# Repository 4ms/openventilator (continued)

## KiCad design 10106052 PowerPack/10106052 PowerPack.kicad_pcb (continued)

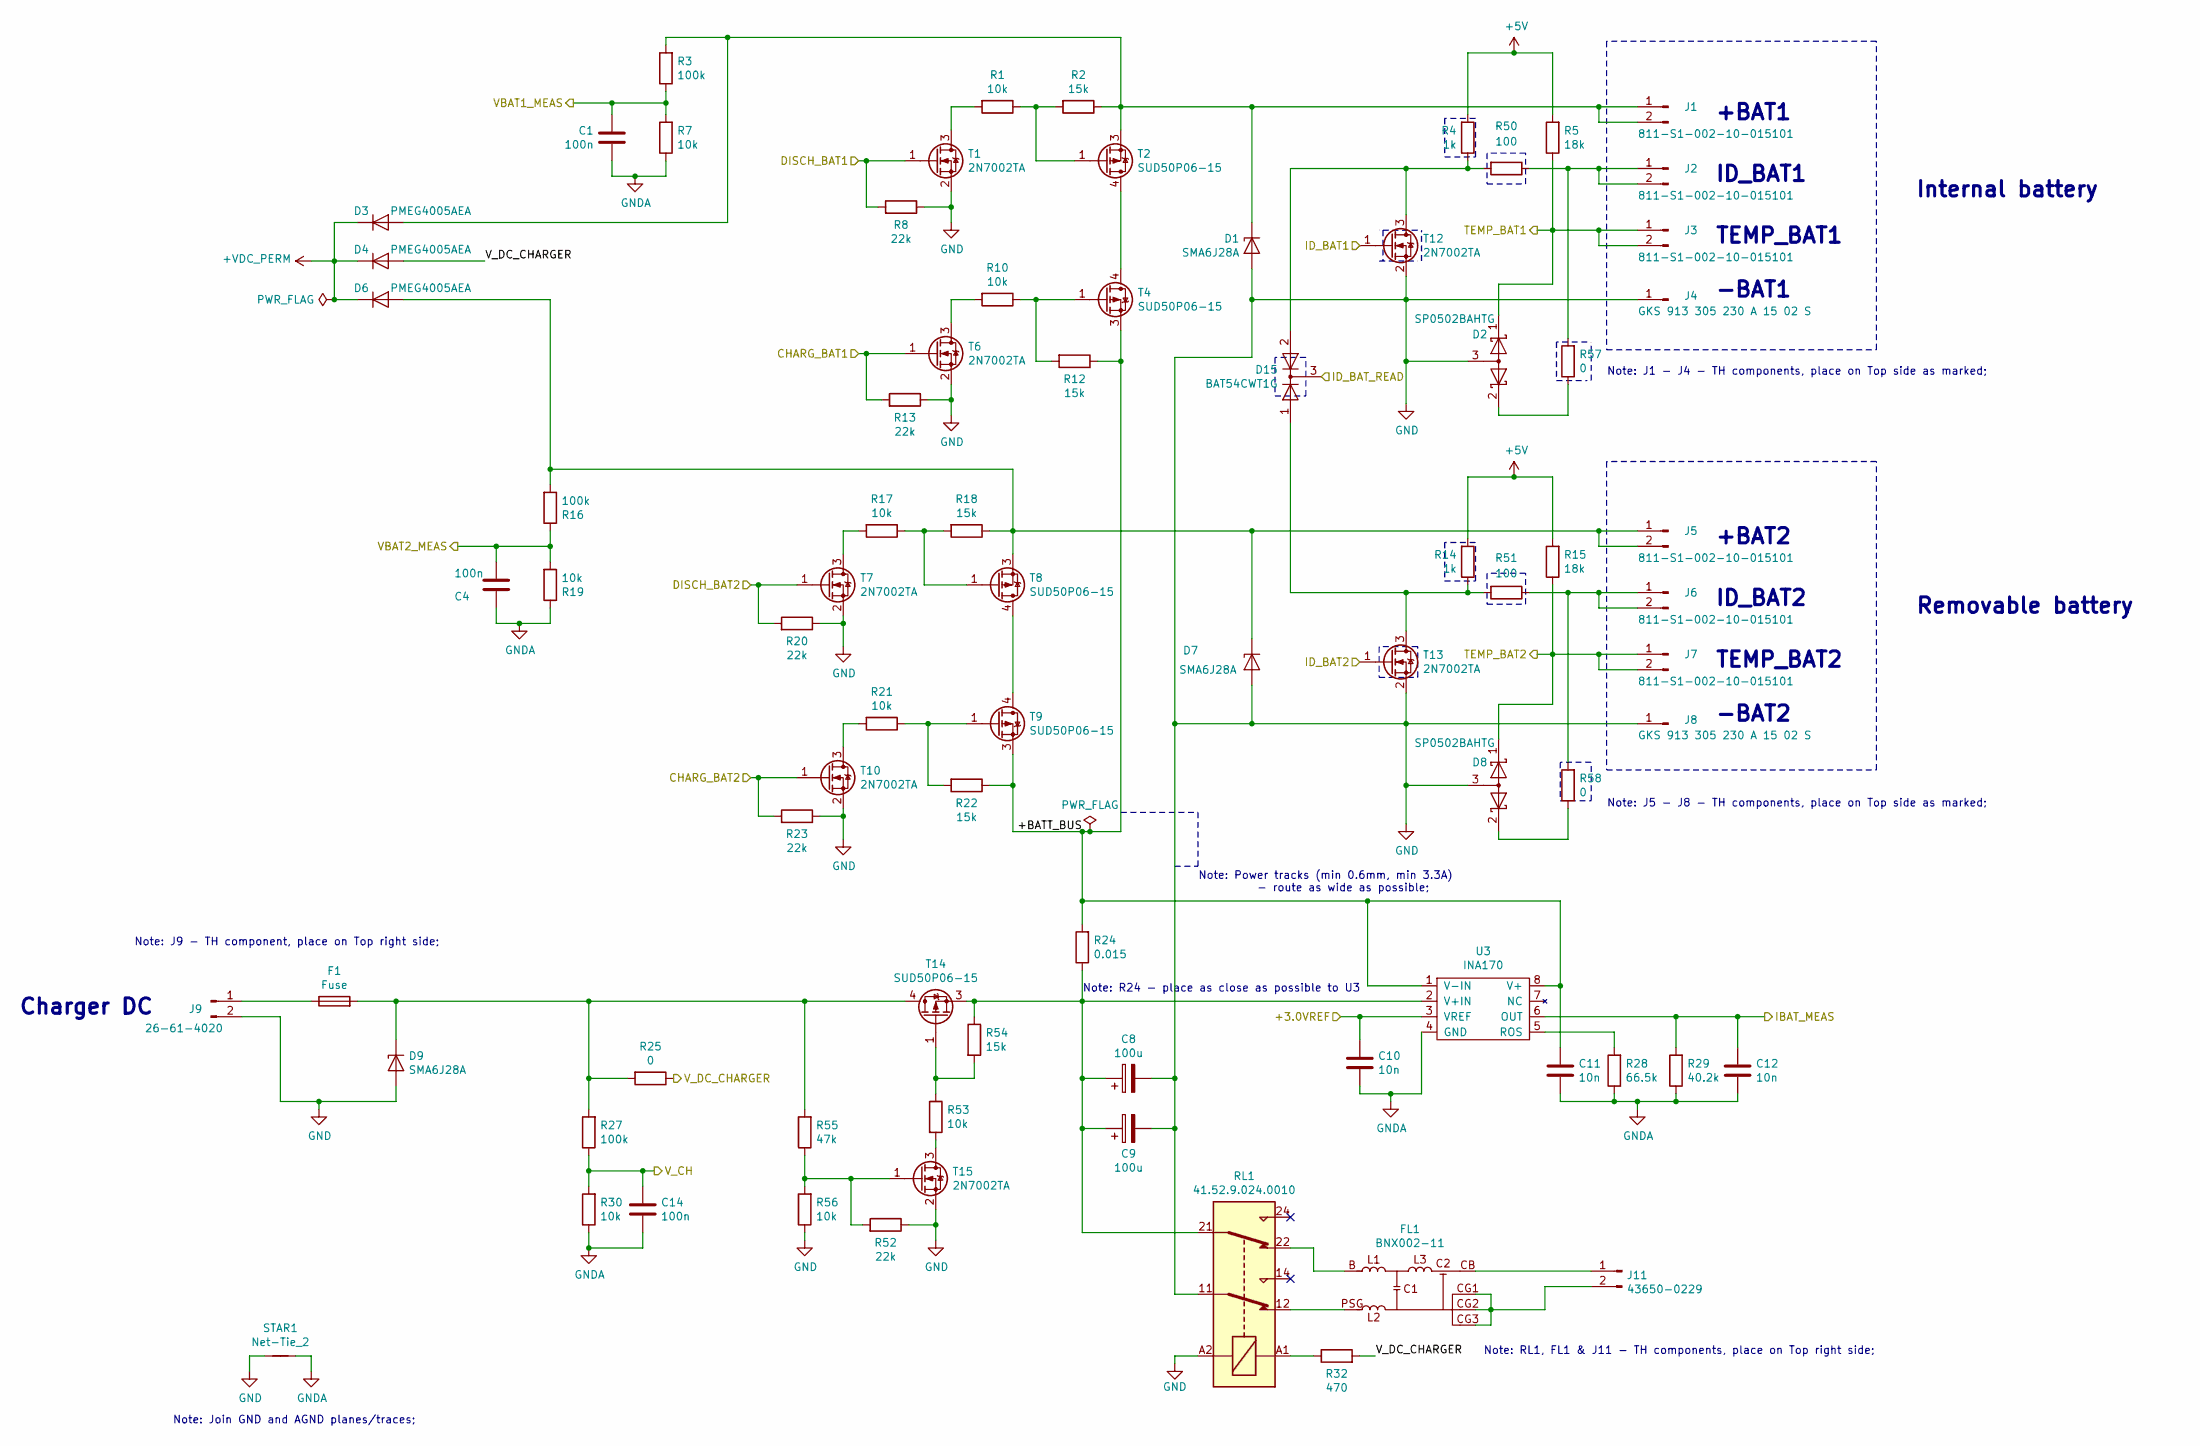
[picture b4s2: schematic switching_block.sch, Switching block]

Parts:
C1, C4, C14: 100n; CAPC1608X86N
C8, C9: 100u; CAPPRD350W60D800H1250
C10, C11, C12: 10n; CAPC1608X86N
D1, D7, D9: SMA6J28A; DIOM5126X203N_SWP
D2, D8: SP0502BAHTG; SOT65P220X110-3N
D3, D4, D6: PMEG4005AEA; SOD2512X110N_SWP
D15: BAT54CWT1G; SOT65P220X110-3N
F1: Fuse; FUS4755X155N
FL1: BNX002-11; BNX00201
J1, J2, J3, J5, J6, J7: 811-S1-002-10-015101; CON254W80L508T254H600P
J4, J8: GKS 913 305 230 A 15 02 S; GKS-913-305-230-A-15-02-S
J9: 26-61-4020; CON2PHDR1000W777L396P
J11: 43650-0229; CON-43650-0229
R1, R7, R10, R17, R19, R21, R30, R53, R56: 10k; RESC1608X50AN
R2, R12, R18, R22, R54: 15k; RESC1608X50AN
R3, R16, R27: 100k; RESC1608X50AN
R4, R14: 1k; RESC1608X50AN
R5, R15: 18k; RESC1608X50AN
R8, R13, R20, R23, R52: 22k; RESC1608X50AN
R24: 0.015; RESC6533X80N
R25: 0; RESC3216X60N
R28: 66.5k; RESC1608X50AN
R29: 40.2k; RESC1608X50AN
R32: 470; RESC3216X60N
R50, R51: 100; CAPC1608X86N
R55: 47k; RESC1608X50AN
R57, R58: 0; RESC1608X50AN
RL1: 41.52.9.024.0010; RLY-41-52-9-024-0010
STAR1: Net-Tie_2; STAR
T1, T6, T7, T10, T12, T13, T15: 2N7002TA; SOT95P237X112-3N
T2, T4, T8, T9, T14: SUD50P06-15; TO228P1003X238-3_4N
U3: INA170; SOP65P490X110-8N

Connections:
+3.0VREF: C10.2, U3.3 (VREF); also elsewhere on the board
+5V: R4.2, R5.2, R14.2, R15.2; also elsewhere on the board
+VDC_PERM: D3.2 (K), D4.2 (K), D6.2 (K); also elsewhere on the board
/CHARG_BAT1: R13.2, T6.1 (G); also elsewhere on the board
/CHARG_BAT2: R23.2, T10.1 (G); also elsewhere on the board
/DISCH_BAT1: R8.2, T1.1 (G); also elsewhere on the board
/DISCH_BAT2: R20.2, T7.1 (G); also elsewhere on the board
/IBAT_MEAS: C12.2, R29.2, U3.6 (OUT); also elsewhere on the board
/ID_BAT1: T12.1 (G); also elsewhere on the board
/ID_BAT2: T13.1 (G); also elsewhere on the board
/ID_BAT_READ: D15.3 (K); also elsewhere on the board
/Switching block/+BATT_BUS: C11.2, R12.1, R22.1, R24.2, T4.3 (S), T9.3 (S), U3.1 (V-IN), U3.8 (V+)
/TEMP_BAT1: D2.1 (K), J3.1, J3.2, R5.1; also elsewhere on the board
/TEMP_BAT2: D8.1 (K), J7.1, J7.2, R15.1; also elsewhere on the board
/VBAT1_MEAS: C1.2, R3.1, R7.2; also elsewhere on the board
/VBAT2_MEAS: C4.2, R16.1, R19.2; also elsewhere on the board
/V_CH: C14.2, R27.1, R30.2; also elsewhere on the board
/V_DC_CHARGER: D4.1 (A), R25.1, R32.2; also elsewhere on the board
GND: C8.2, C9.2, D1.1 (A), D2.3 (A), D7.1 (A), D8.3 (A), D9.1 (A), J4.1, J8.1, J9.2, R8.1, R13.1, R20.1, R23.1, R52.1, R56.1, RL1.11, RL1.A2, STAR1.1, T1.2 (S), T6.2 (S), T7.2 (S), T10.2 (S), T12.2 (S), T13.2 (S), T15.2 (S); also elsewhere on the board
GNDA: C1.1, C4.1, C10.1, C11.1, C12.1, C14.1, R7.1, R19.1, R28.1, R29.1, R30.1, STAR1.2, U3.4 (GND); also elsewhere on the board
unnamed: C8.1, C9.1, R24.1, R54.1, RL1.21, T14.3 (S), U3.2 (V+IN)
unnamed: D1.2 (K), D3.1 (A), J1.1, J1.2, R2.1, R3.2, T2.3 (S)
unnamed: D2.2 (K), R57.1
unnamed: D6.1 (A), D7.2 (K), J5.1, J5.2, R16.2, R18.1, T8.3 (S)
unnamed: D8.2 (K), R58.1
unnamed: D9.2 (K), F1.2, R25.2, R27.2, R55.2, T14.4 (D)
unnamed: D15.1 (A), R14.1, R51.2, T13.3 (D)
unnamed: D15.2 (A), R4.1, R50.2, T12.3 (D)
unnamed: F1.1, J9.1
unnamed: FL1.B, RL1.22
unnamed: FL1.CB, J11.1
unnamed: FL1.CG1, FL1.CG2, FL1.CG3, J11.2
unnamed: FL1.PSG, RL1.12
unnamed: J2.1, J2.2, R50.1, R57.2
unnamed: J6.1, J6.2, R51.1, R58.2
unnamed: R1.1, R2.2, T2.1 (G)
unnamed: R1.2, T1.3 (D)
unnamed: R10.1, R12.2, T4.1 (G)
unnamed: R10.2, T6.3 (D)
unnamed: R17.1, R18.2, T8.1 (G)
unnamed: R17.2, T7.3 (D)
unnamed: R21.1, R22.2, T9.1 (G)
unnamed: R21.2, T10.3 (D)
unnamed: R28.2, U3.5 (ROS)
unnamed: R32.1, RL1.A1
unnamed: R52.2, R55.1, R56.2, T15.1 (G)
unnamed: R53.1, R54.2, T14.1 (G)
unnamed: R53.2, T15.3 (D)
unnamed: T2.4 (D), T4.4 (D)
unnamed: T8.4 (D), T9.4 (D)

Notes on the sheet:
ID_BAT2
TEMP_BAT2
+BAT1
ID_BAT1
TEMP_BAT1
-BAT1
Internal battery
Removable battery
Note: J1 - J4 - TH components, place on Top side as marked;
Note: J5 - J8 - TH components, place on Top side as marked;
Note: Power tracks (min 0.6mm, min 3.3A) - route as wide as possible;
Note: RL1, FL1 & J11 - TH components, place on Top right side;
Charger DC
Note: J9 - TH component, place on Top right side;
Note: R24 - place as close as possible to U3
Note: Join GND and AGND planes/traces;
+BAT2
-BAT2

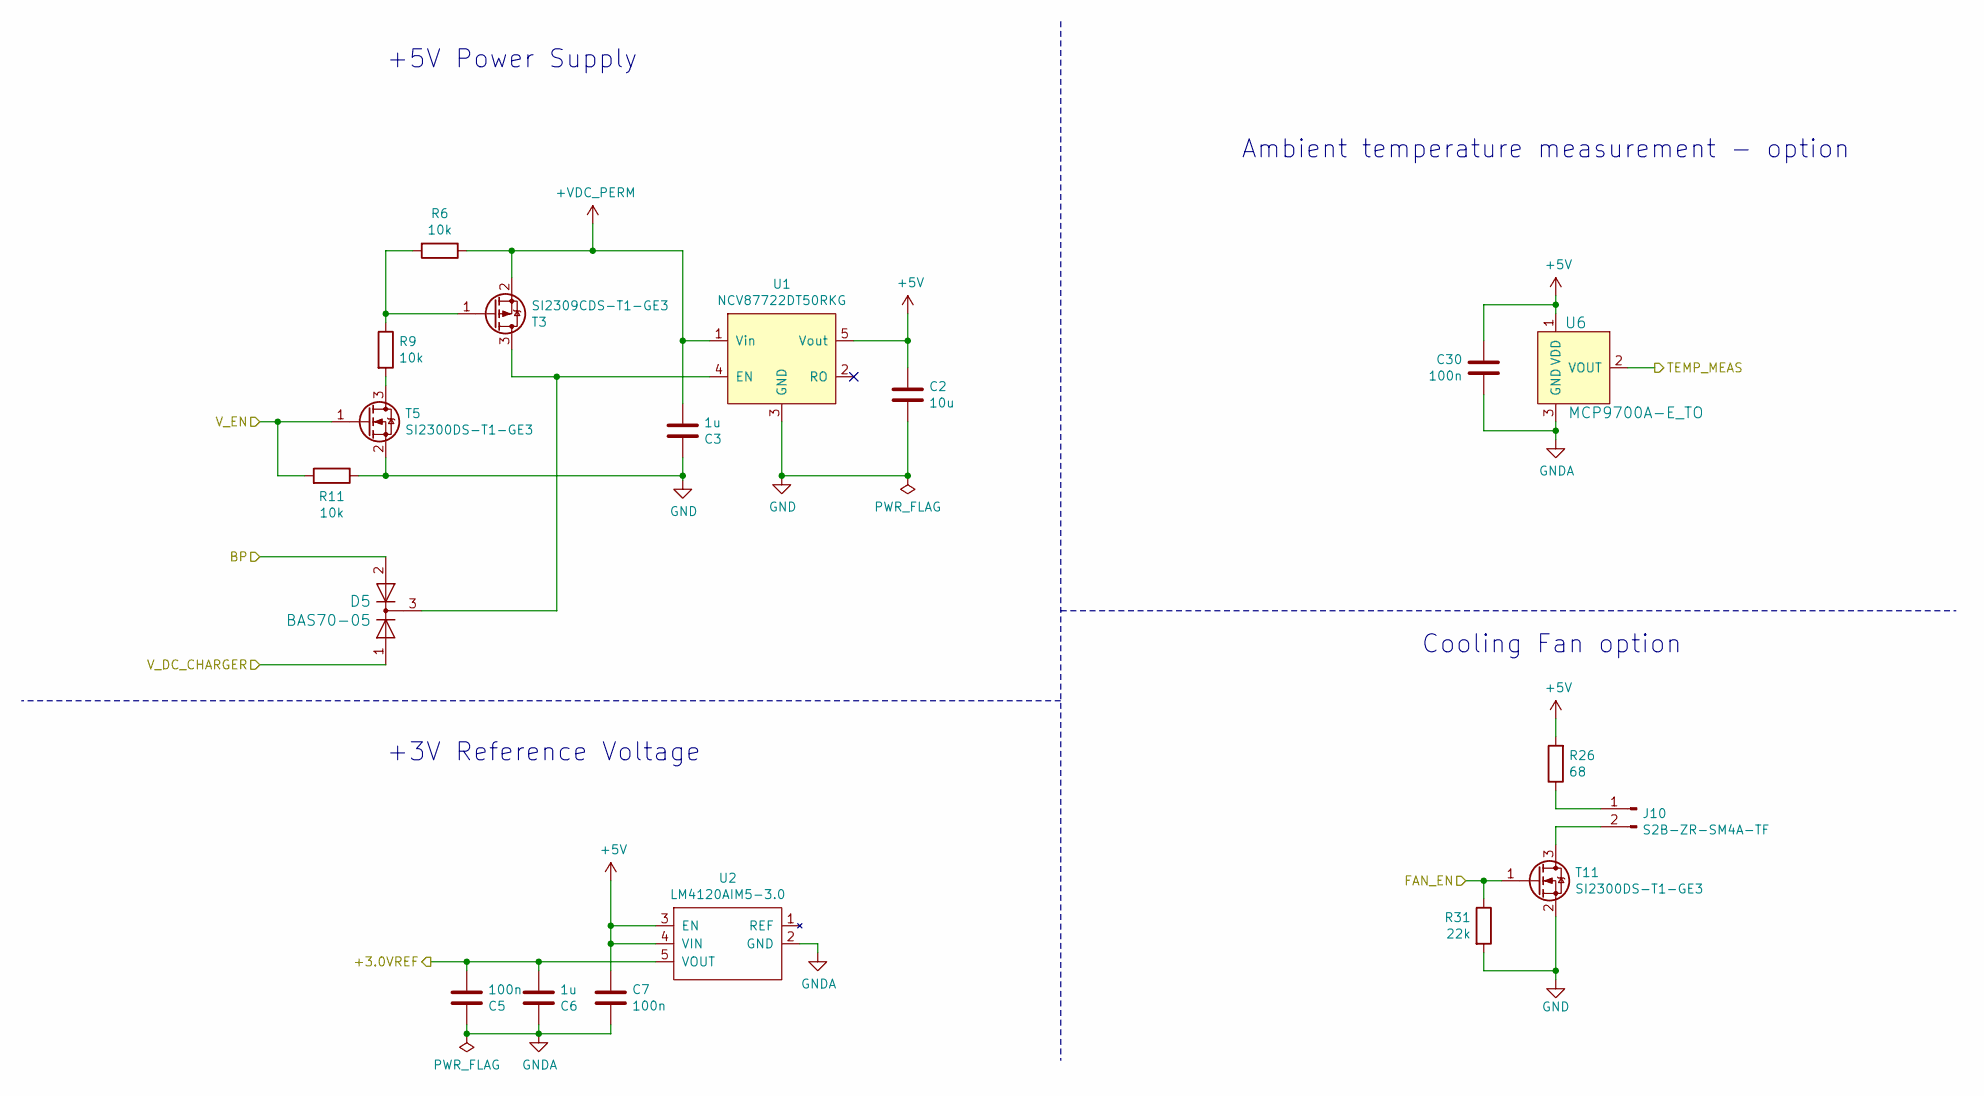
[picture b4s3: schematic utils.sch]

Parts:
C2: 10u; CAPC1608X86N
C3: 1u; CAPC3225X155N
C5, C7, C30: 100n; CAPC1608X86N
C6: 1u; CAPC1005X60N
D5: BAS70-05; SOT92P240X120-3N
J10: S2B-ZR-SM4A-TF; CON-S2B-ZR-SM4A-TF
R6, R9, R11: 10k; RESC1608X50AN
R26: 68; RESC3216X60N
R31: 22k; RESC1608X50AN
T3: SI2309CDS-T1-GE3; SOT95P237X112-3N
T5, T11: SI2300DS-T1-GE3; SOT95P237X112-3N
U1: NCV87722DT50RKG; TO170P1420X457-8NA
U2: LM4120AIM5-3.0; SOT95P279X142-5N
U6: MCP9700A-E_TO; TO-92; Digi-Key_PN MCP9700A-E/TO-ND

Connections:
+3.0VREF: C5.2, C6.2, U2.5 (VOUT); also elsewhere on the board
+5V: C2.2, C7.2, C30.2, R26.2, U1.5 (Vout), U2.3 (EN), U2.4 (VIN), U6.1 (VDD); also elsewhere on the board
+VDC_PERM: C3.2, R6.1, T3.2 (S), U1.1 (Vin); also elsewhere on the board
/BP: D5.2 (A); also elsewhere on the board
/FAN_EN: R31.1, T11.1 (G); also elsewhere on the board
/TEMP_MEAS: U6.2 (VOUT); also elsewhere on the board
/V_DC_CHARGER: D5.1 (A); also elsewhere on the board
/V_EN: R11.2, T5.1 (G); also elsewhere on the board
GND: C2.1, C3.1, R11.1, R31.2, T5.2 (S), T11.2 (S), U1.3 (GND); also elsewhere on the board
GNDA: C5.1, C6.1, C7.1, C30.1, U2.2 (GND), U6.3 (GND); also elsewhere on the board
unnamed: D5.3 (K), T3.3 (D), U1.4 (EN)
unnamed: J10.1, R26.1
unnamed: J10.2, T11.3 (D)
unnamed: R6.2, R9.1, T3.1 (G)
unnamed: R9.2, T5.3 (D)

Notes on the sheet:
Ambient temperature measurement - option
Cooling Fan option
+5V Power Supply
+3V Reference Voltage

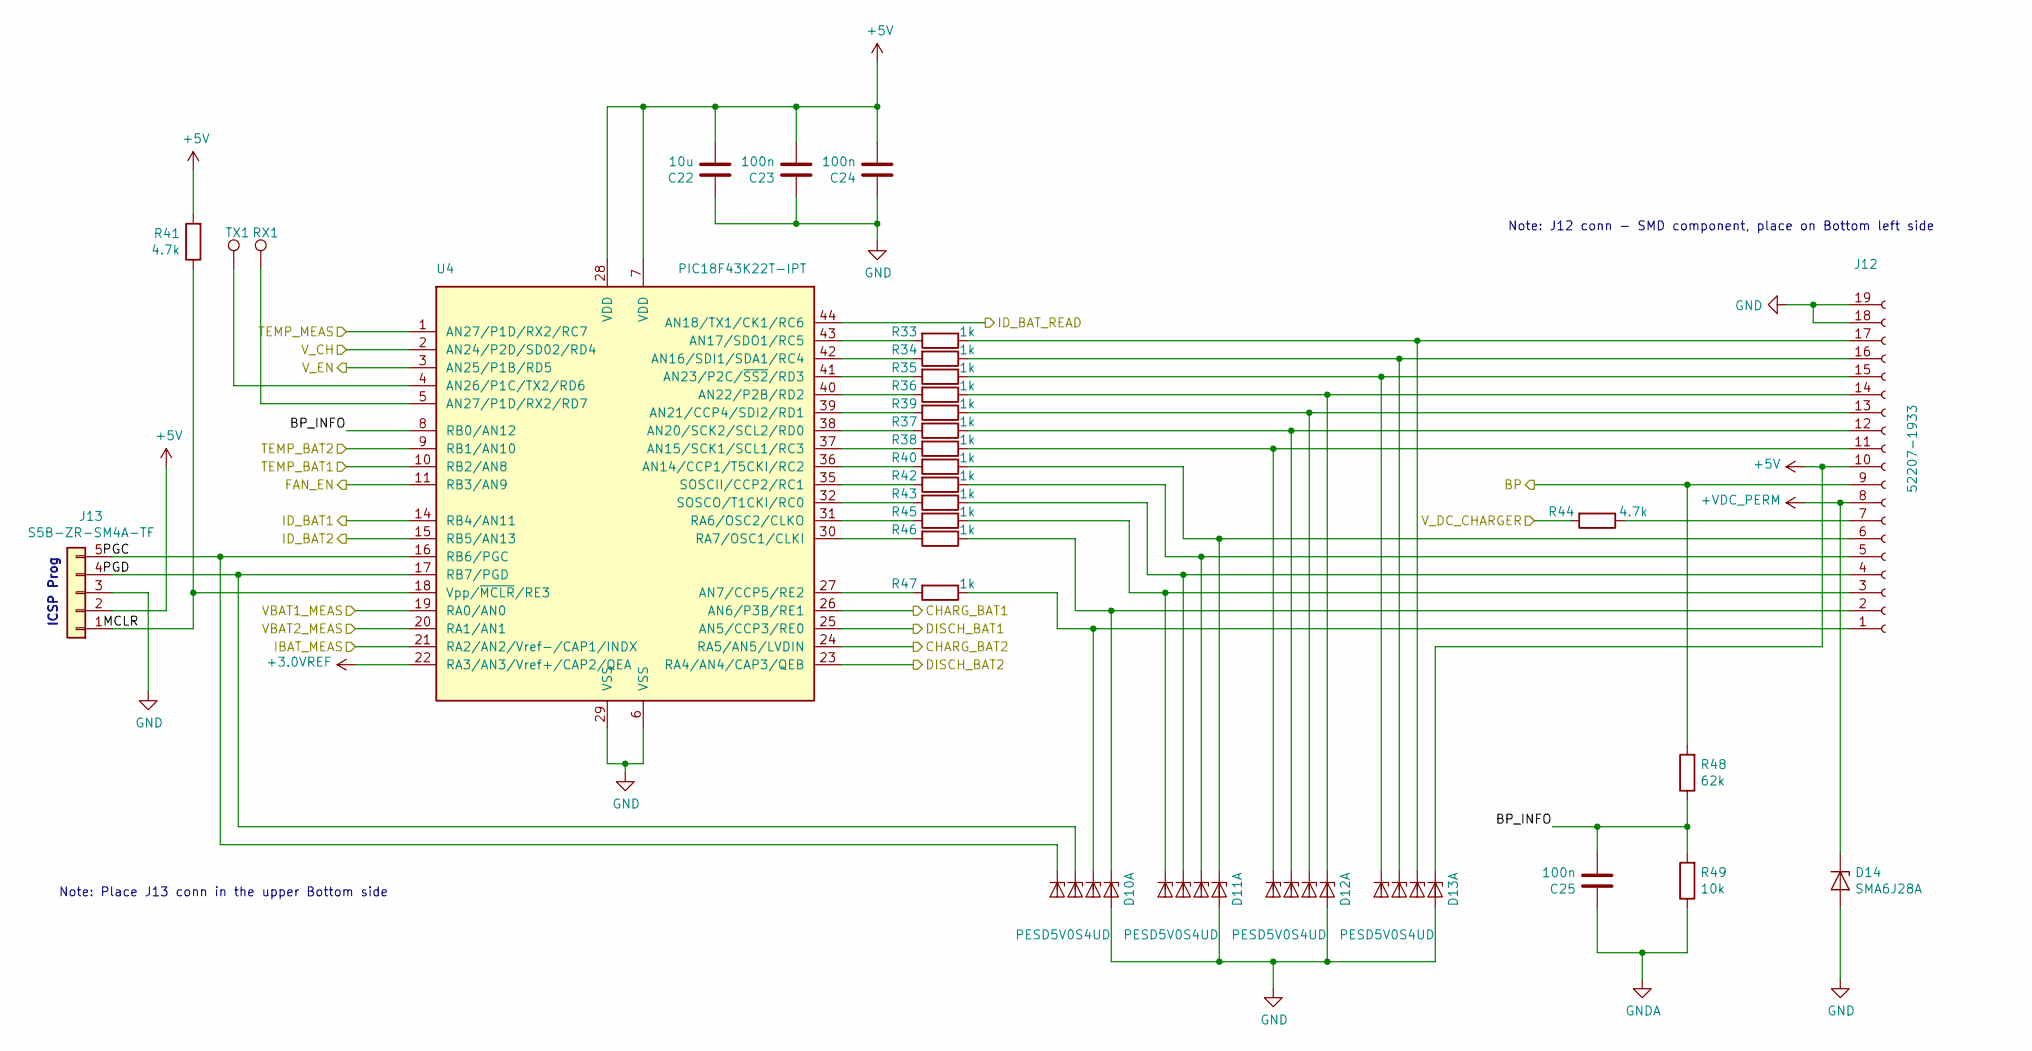
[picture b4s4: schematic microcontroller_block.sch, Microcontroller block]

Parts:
C22: 10u; CAPC1608X86N
C23, C24, C25: 100n; CAPC1608X86N
D10, D11, D12, D13: PESD5V0S4UD; SOT95P275X110-6N
D14: SMA6J28A; DIOM5126X203N_SWP
J12: Molex_52207-1933_1x19-1MP_P1.00mm_Horizontal; CON-52207-1960; Manufacturer_PartNo 52207-1933
J13: S5B-ZR-SM4A-TF; CON-S5B-ZR-SM4A-TF
R33, R34, R35, R36, R37, R38, R39, R40, R42, R43, R45, R46, R47: 1k; RESC1608X50AN; Tolerance 1%
R41: 4.7k; RESC1608X50AN; Tolerance 1%
R44: 4.7k; RESC3216X60N; Tolerance 5%
R48: 62k; RESC1608X50AN; Tolerance 1%
R49: 10k; RESC1608X50AN; Tolerance 1%
RX1: TestPoint; TP-40R-NSA
TX1: TestPoint; TP-40R-NSA
U4: PIC18F43K22T-IPT; QFP80P1200X1200X120-44N

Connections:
+3.0VREF: U4.22 (RA3/AN3/Vref+/CAP2/QEA); also elsewhere on the board
+5V: C22.2, C23.2, C24.2, D13.1 (K1), J12.10, J13.2, R41.2, U4.7 (VDD), U4.28 (VDD); also elsewhere on the board
+VDC_PERM: D14.2 (K), J12.8; also elsewhere on the board
/BP: J12.9, R48.2; also elsewhere on the board
/CHARG_BAT1: U4.26 (AN6/P3B/RE1); also elsewhere on the board
/CHARG_BAT2: U4.24 (RA5/AN5/LVDIN); also elsewhere on the board
/DISCH_BAT1: U4.25 (AN5/CCP3/RE0); also elsewhere on the board
/DISCH_BAT2: U4.23 (RA4/AN4/CAP3/QEB); also elsewhere on the board
/FAN_EN: U4.11 (RB3/AN9); also elsewhere on the board
/IBAT_MEAS: U4.21 (RA2/AN2/Vref-/CAP1/INDX); also elsewhere on the board
/ID_BAT1: U4.14 (RB4/AN11); also elsewhere on the board
/ID_BAT2: U4.15 (RB5/AN13); also elsewhere on the board
/ID_BAT_READ: U4.44 (AN18/TX1/CK1/RC6); also elsewhere on the board
/Microcontroller block/BP_INFO: C25.2, R48.1, R49.2, U4.8 (RB0/AN12)
/Microcontroller block/MCLR: J13.1, R41.1, U4.18 (Vpp/~MCLR~/RE3)
/Microcontroller block/PGC: D10.6 (K4), J13.5, U4.16 (RB6/PGC)
/Microcontroller block/PGD: D10.4 (K3), J13.4, U4.17 (RB7/PGD)
/TEMP_BAT1: U4.10 (RB2/AN8); also elsewhere on the board
/TEMP_BAT2: U4.9 (RB1/AN10); also elsewhere on the board
/TEMP_MEAS: U4.1 (AN27/P1D/RX2/RC7); also elsewhere on the board
/VBAT1_MEAS: U4.19 (RA0/AN0); also elsewhere on the board
/VBAT2_MEAS: U4.20 (RA1/AN1); also elsewhere on the board
/V_CH: U4.2 (AN24/P2D/SD02/RD4); also elsewhere on the board
/V_DC_CHARGER: R44.2; also elsewhere on the board
/V_EN: U4.3 (AN25/P1B/RD5); also elsewhere on the board
GND: C22.1, C23.1, C24.1, D10.2 (A), D10.5 (A), D11.2 (A), D11.5 (A), D12.2 (A), D12.5 (A), D13.2 (A), D13.5 (A), D14.1 (A), J12.18, J12.19, J13.3, U4.6 (VSS), U4.29 (VSS); also elsewhere on the board
GNDA: C25.1, R49.1; also elsewhere on the board
unnamed: D10.1 (K1), J12.2, R46.1
unnamed: D10.3 (K2), J12.1, R47.1
unnamed: D11.1 (K1), J12.6, R40.1
unnamed: D11.3 (K2), J12.5, R42.1
unnamed: D11.4 (K3), J12.4, R43.1
unnamed: D11.6 (K4), J12.3, R45.1
unnamed: D12.1 (K1), J12.14, R36.1
unnamed: D12.3 (K2), J12.13, R39.1
unnamed: D12.4 (K3), J12.12, R37.1
unnamed: D12.6 (K4), J12.11, R38.1
unnamed: D13.3 (K2), J12.17, R33.1
unnamed: D13.4 (K3), J12.16, R34.1
unnamed: D13.6 (K4), J12.15, R35.1
unnamed: J12.7, R44.1
unnamed: R33.2, U4.43 (AN17/SDO1/RC5)
unnamed: R34.2, U4.42 (AN16/SDI1/SDA1/RC4)
unnamed: R35.2, U4.41 (AN23/P2C/~SS2~/RD3)
unnamed: R36.2, U4.40 (AN22/P2B/RD2)
unnamed: R37.2, U4.38 (AN20/SCK2/SCL2/RD0)
unnamed: R38.2, U4.37 (AN15/SCK1/SCL1/RC3)
unnamed: R39.2, U4.39 (AN21/CCP4/SDI2/RD1)
unnamed: R40.2, U4.36 (AN14/CCP1/T5CKI/RC2)
unnamed: R42.2, U4.35 (SOSCII/CCP2/RC1)
unnamed: R43.2, U4.32 (SOSCO/T1CKI/RC0)
unnamed: R45.2, U4.31 (RA6/OSC2/CLKO)
unnamed: R46.2, U4.30 (RA7/OSC1/CLKI)
unnamed: R47.2, U4.27 (AN7/CCP5/RE2)
unnamed: RX1.1, U4.5 (AN27/P1D/RX2/RD7)
unnamed: TX1.1, U4.4 (AN26/P1C/TX2/RD6)

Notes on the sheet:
Note: Place J13 conn in the upper Bottom side
Note: J12 conn - SMD component, place on Bottom left side
ICSP Prog

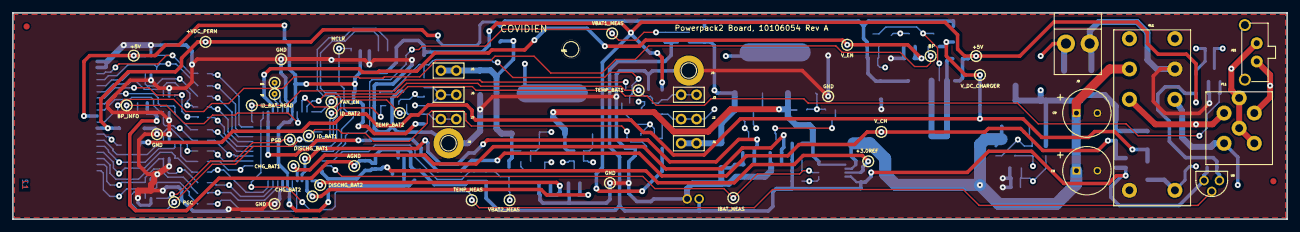
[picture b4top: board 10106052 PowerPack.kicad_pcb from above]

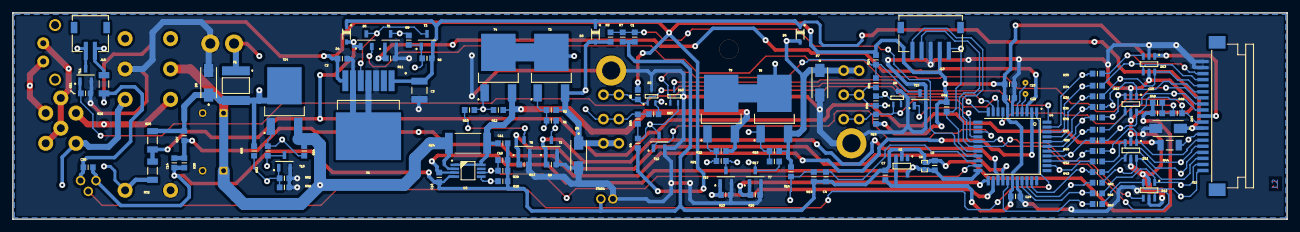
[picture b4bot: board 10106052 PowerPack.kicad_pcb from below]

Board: 2 copper layers, 210.0 x 34.0 mm, 133 parts (113 on the bottom side), 92 nets.

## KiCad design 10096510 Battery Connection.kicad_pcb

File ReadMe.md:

# OpenVentilator

This project is a collaboration to update the OpenVentilator files provided by Medtronic to modern KiCad format as well as update BoM to currently available components.

If you'd like to contribute, please contact Seth (seth@kipro-pcb.com) for details.

## Getting Started

This includes links to useful resources and defines prerequisite programs or tools for contributing.

### SSH Keys

It is recommended to use a [SSH key](https://docs.gitlab.com/ee/gitlab-basics/create-your-ssh-keys.html) to pull/push.

For Windows users, [follow these instructions](https://docs.joyent.com/public-cloud/getting-started/ssh-keys/generating-an-ssh-key-manually/manually-generating-your-ssh-key-in-windows) to create an SSH key.

### Useful Resources

[Google Drive](https://drive.google.com/drive/folders/1fBbcaIb6aupdgDmfqB_Z8kfAjUOgFtCi) - Project specific Google drive.

[Medtronic Releases](https://www.medtronic.com/us-en/e/open-files/thank-you.html)

[GitLab basics guides](https://docs.gitlab.com/ee/gitlab-basics/)

[Gitflow](https://datasift.github.io/gitflow/IntroducingGitFlow.html)

### Tools

Install [Git](https://git-scm.com/) on your computer.

Either use KiCAD version 5.1.5 or the nightly builds.

[KiCAD v5.1.5](https://kicad-pcb.org/download/) - preferred

[KiCAD Nigthly Builds](https://launchpad.net/~js-reynaud/+archive/ubuntu/ppa-kicad)

**GerbView** - part of KiCAD.

The files need to have 4-quad circles set.  If you add the command `G75*` before the first draw command in each file, gerbview will display correctly.
File → Open Gerber Files. In “File Name” select *.phd for CR-5000 designs.

[PentaLogix ViewMate Free (Windows)](https://www.pentalogix.com/t/software-products/viewmate) 

You will need to create an account to download and get a serial number. Run File → Import → Gerber and then control-select all the .phd files for CR-5000 designs.

[GerberLogix](https://www.easylogix.de/products_detail.php?prog_id=1)

Works well with the free version for .phd files.  A little simpler than ViewMate

## Contributing

Please read [Contributing.md](Contributing.md) for information on cloning, branching, and sharing your work.

## Versioning

We should adhere to [SemVer](https://semver.org/) for our versioning process. Each PCB will have its own version number.

*Note that this is not completely settled.*

## Channels and Leads

If you are interested in working on a specific board, please head to the respective channels in the Slack organization. The leads for each board are provided below as well.

Be sure to check for pinned messages as well as the channel topic for more information as well.

### Hardware
**#battery-connection-board** for the Battery Connection Board. Lead by Valerie Hanson.

**#blower-driver-board** for the Blower Command Board. Lead by Gabe Soares.

**#buzzer-board** for the Buzzer Board RB0505. Lead by Yannick Liotta.

**#cpu-board** for the CPU Board. Lead by Seth Hillbrand.

**#mechanical-prototyping** for all mechanical components. Currently no lead.

**#power-management-board** for the Power Supply Board (Tantalum Less). Lead by Paul Petersen.

**#powerpack-board** for the Power Pack Board. Lead by George Ioakimedes.

**#turbine** for the blower turbine motor. Currently no lead.

### Firmware
**#firmware-pic** for questions relating to the PIC Firmware. Currently no lead.

**#firmware-st10** for questions relating to the ST Micro Firmware. Lead by Melvin Aguirre.

### Project Related
**#how-to-get-started** for help in setting up any part of the project. Lead by Adam Drewery.

**#general** for questions that you're unsure where they would belong.

**#openventilator** for high-level project discussions. For example, what version of KiCAD to use?

**#parts** for any questions related to parts. This can be creating them in KiCAD or sourcing them. For sourcing contact Ritika Sahai-Kar or Sophi Kravitz. For parts creation contact Adam Drewery.

## Parts

If creating new parts, follow the [KiCAD Library Convention](https://kicad-pcb.org/libraries/klc/).

Passives are an exception to this rule. Please create a library part per MPN.

### Symbol Parameters

The following fields are *required* for all parts.

**Reference**

**Value**

**Footprint**

**Documentation**

**Description**

**Item Number** - This is Medtronic's Item Number called out in their documentation.

**Manufacturer**

**Manufacturer_No**

### Pointing to the right libraries

Be sure you are not pointing to your own libraries. We want to work within the OpenVentilator project library.

Within a KiCAD project, click on Preferences -> Manage Symbol Libraries.

The Path to the libraries should contain **${KIPRJMOD}**.

*Note: The libraries are ultimately going to be brought into their own directory in the project. We will keep you posted with more information.*

## License

This project is licensed under the [Permissive License - Open Ventilator](Permissive License--Open Ventilator.pdf).

## Acknowledgements

Thanks to Marc Hillman for his contribution to the Battery Connection Board.

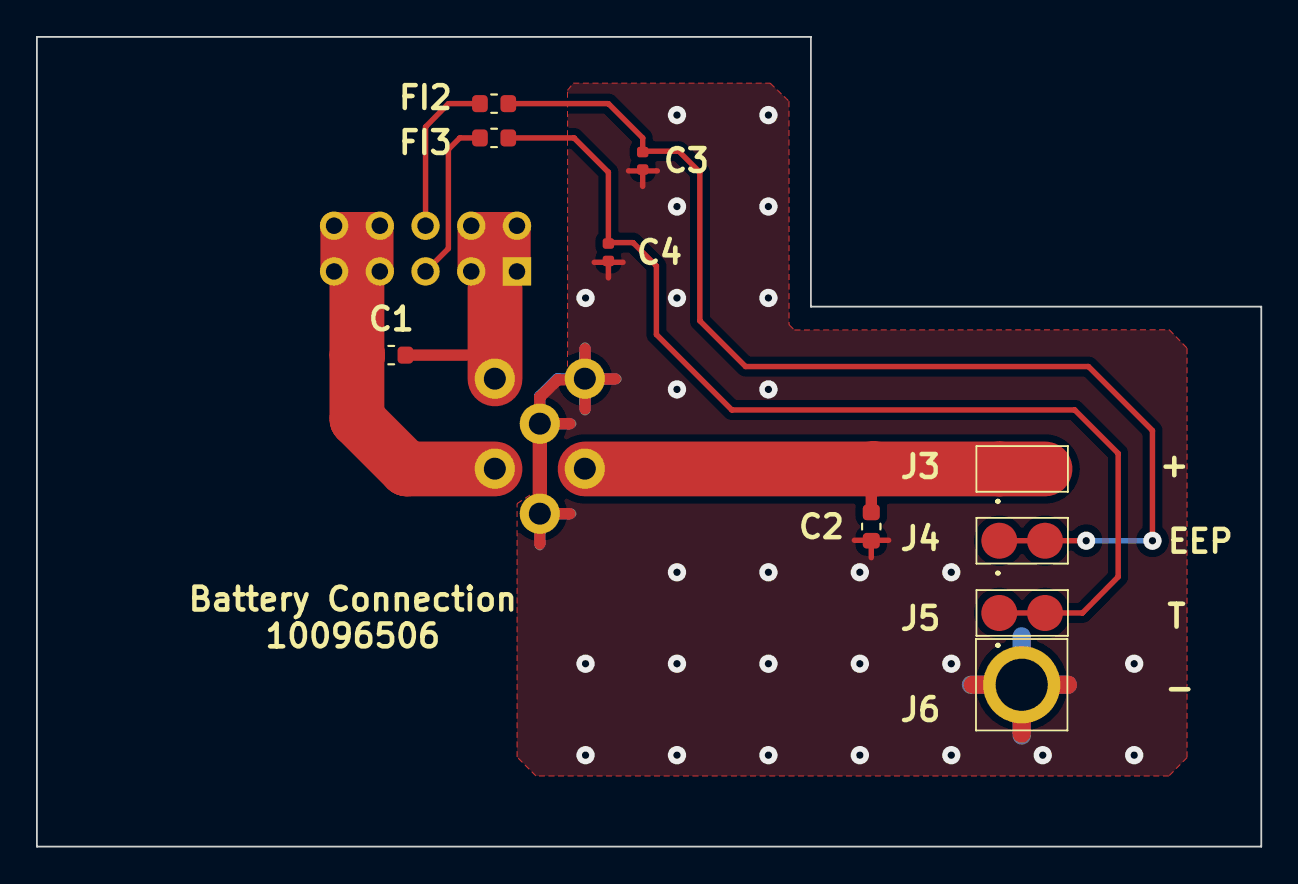
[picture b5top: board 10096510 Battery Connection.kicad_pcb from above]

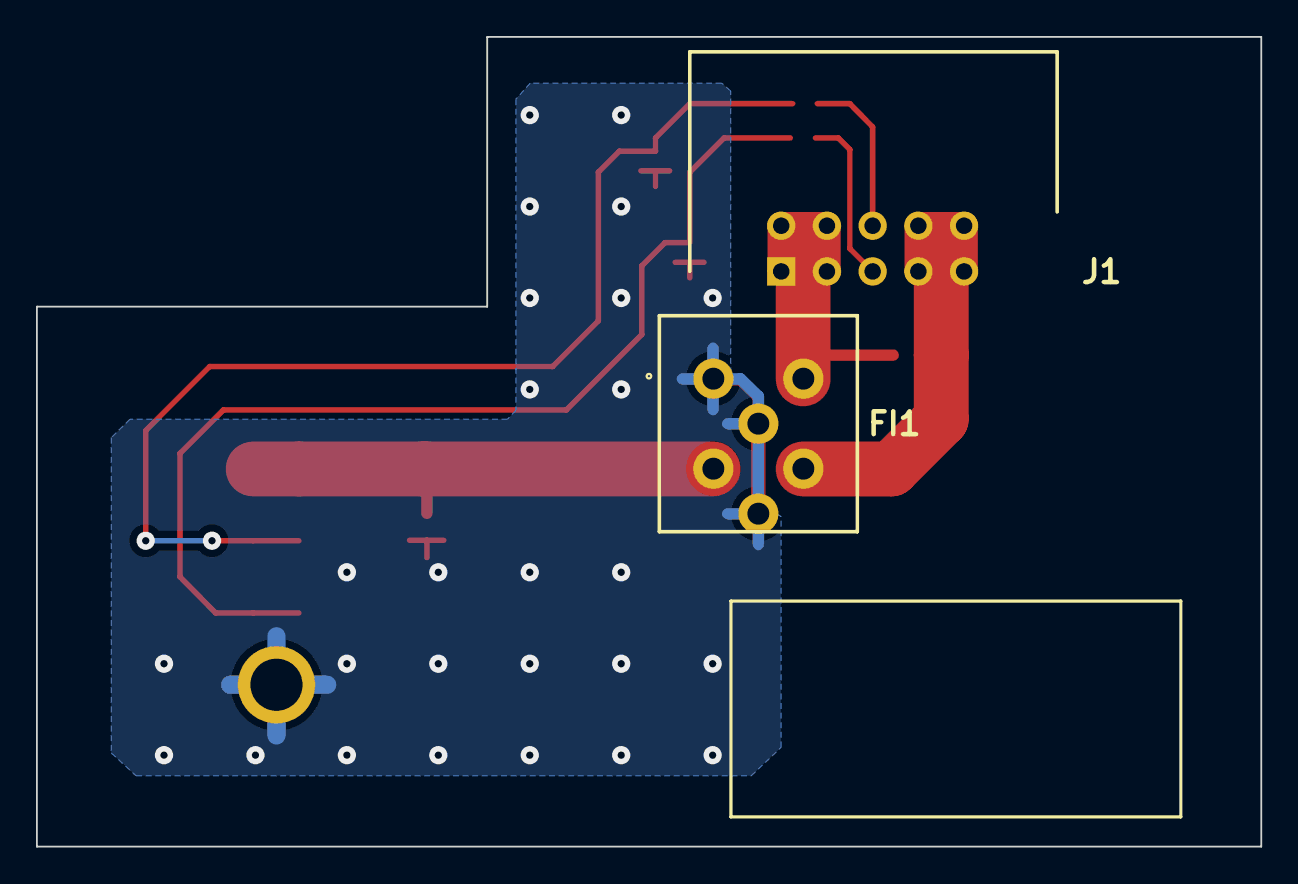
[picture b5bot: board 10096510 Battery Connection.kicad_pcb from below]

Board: 2 copper layers, 68.0 x 45.0 mm, 12 parts (2 on the bottom side), 8 nets.

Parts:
C1, C2: 10nF; C_0603_1608Metric
C3, C4: 0402_47pF_C0402C470J5GAC; C_0402_1005Metric
FI1: BNX002-11; BNX002-011
FI2, FI3: 74279266; L_0603_1608Metric
J1: 09185107323; SHDRRA10W64P254_2X5_2050X890X930P
J3, J4, J5: 811-S1-002-30-014101; CONN_811S100230014101
J6: GKS-913-0024; CONN_GKS-913-Z

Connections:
/+: C2.2, FI1.2, J3.1, J3.2
/BAT_EEPROM: C3.1, FI2.1, J4.1, J4.2
/T: C4.1, FI3.2, J5.1, J5.2
Earth: C1.1, FI1.3, J1.1, J1.2, J1.3, J1.4
GND: C2.1, C3.2, C4.2, FI1.4, FI1.5, FI1.6, J6.1
unnamed: FI2.2, J1.6
unnamed: FI3.1, J1.5
VDD: C1.2, FI1.1, J1.7, J1.8, J1.9, J1.10

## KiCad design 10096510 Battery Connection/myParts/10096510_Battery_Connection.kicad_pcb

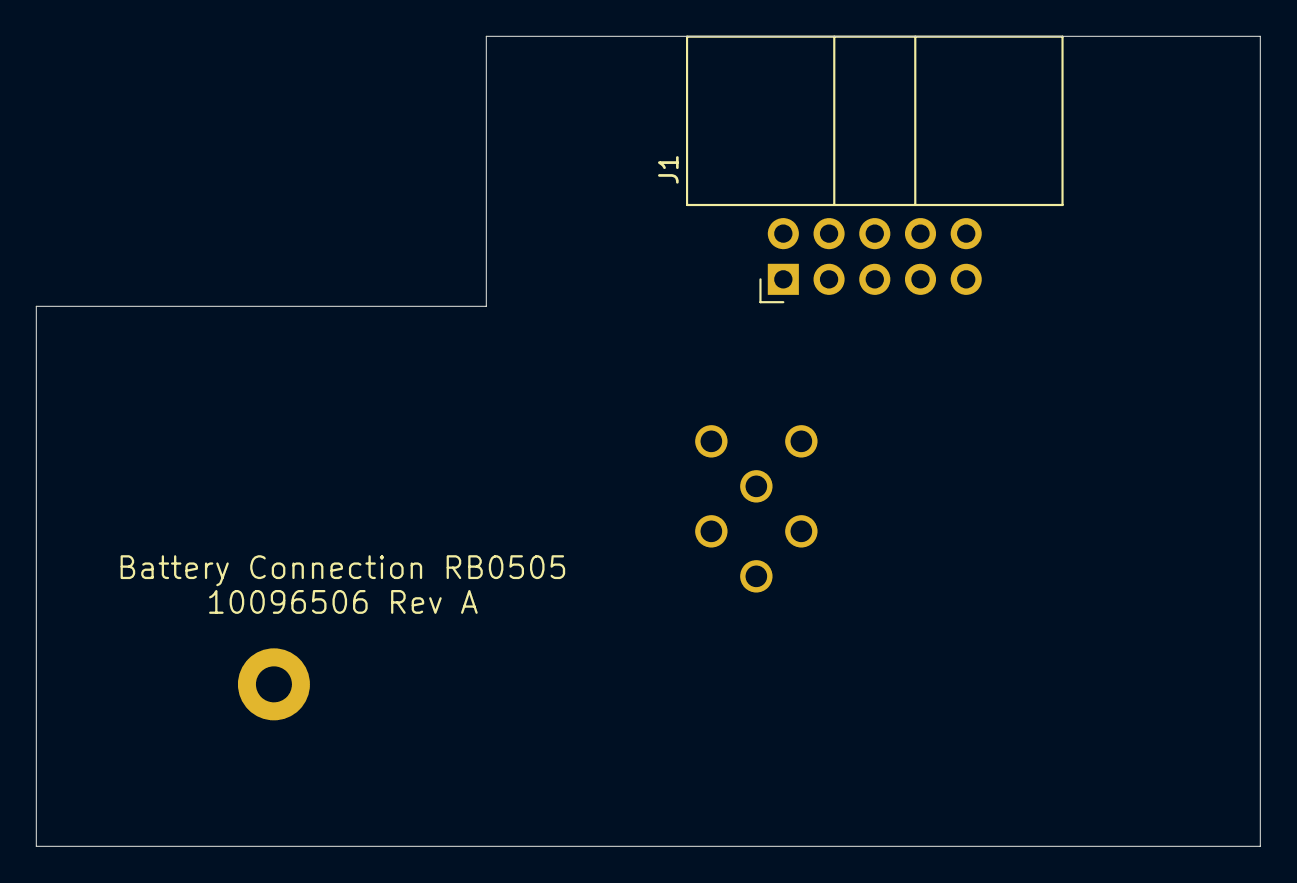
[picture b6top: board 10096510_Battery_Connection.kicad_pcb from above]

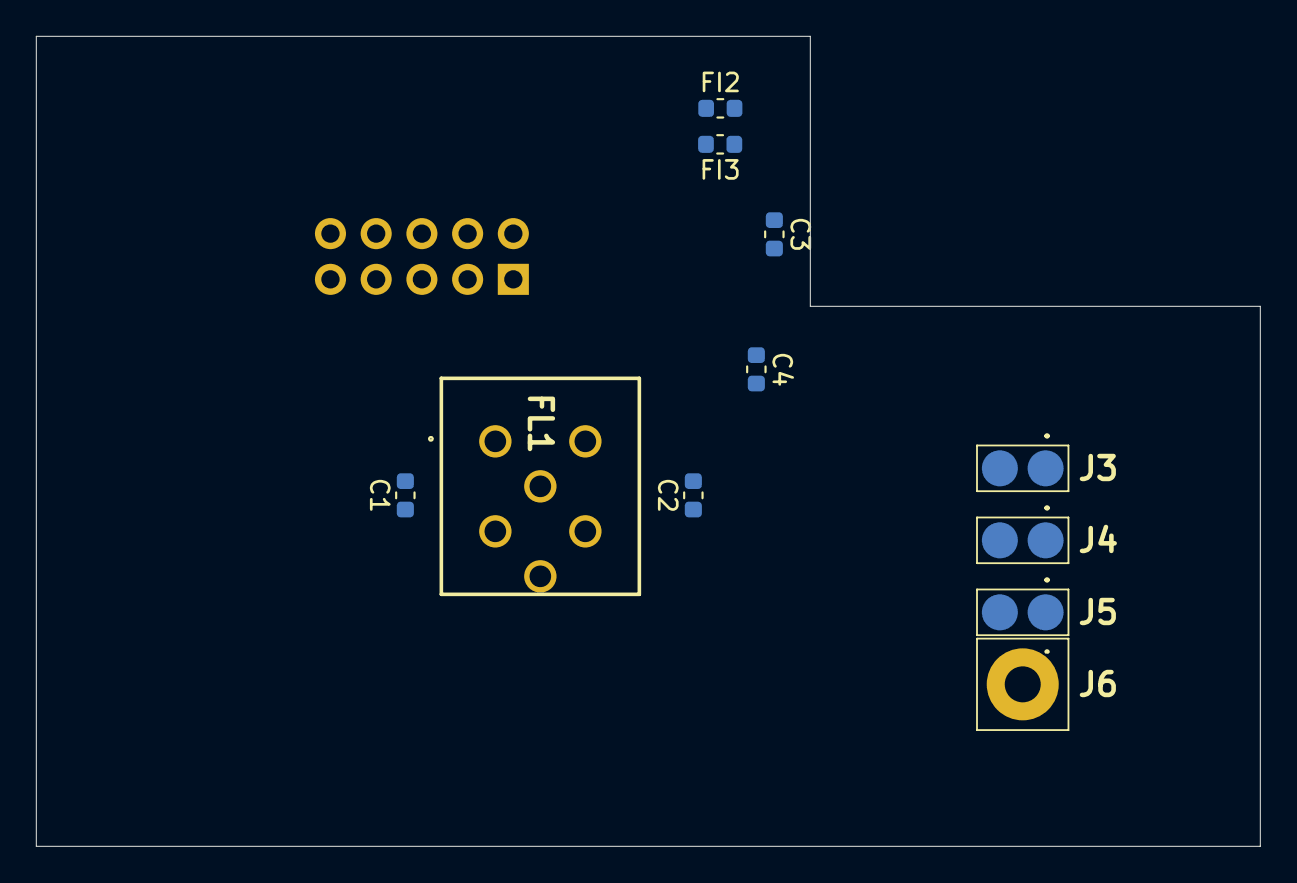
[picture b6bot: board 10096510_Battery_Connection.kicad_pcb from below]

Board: 4 copper layers, 68.0 x 45.0 mm, 12 parts (11 on the bottom side), 8 nets, no tracks yet.

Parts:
C1, C2: 10nF; C_0603_1608Metric
C3, C4: 47pF; C_0603_1608Metric
FI2, FI3: Ferrite bead; R_0603_1608Metric
FL1: BNX002-01
J1: Conn_02x05_Odd_Even; IDC-Header_2x05_P2.54mm_Horizontal
J3: +; 811S100230014101
J4: BAT_EEPROM; 811S100230014101
J5: T; 811S100230014101
J6: GND; GKS-913-Z

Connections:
unnamed: C1.1, FL1.5, J1.7, J1.8, J1.9, J1.10
unnamed: C1.2, FL1.2, J1.1, J1.2, J1.3, J1.4
unnamed: C2.1, FL1.4, J3.1, J3.2
unnamed: C2.2, C3.2, C4.2, FL1.1, FL1.3, FL1.6, J6.1
unnamed: C3.1, FI2.2, J4.1, J4.2
unnamed: C4.1, FI3.1, J5.1, J5.2
unnamed: FI2.1, J1.6
unnamed: FI3.2, J1.5
